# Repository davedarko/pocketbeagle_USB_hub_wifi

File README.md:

# pocketbeagle_USB_hub_wifi
WiFi cape for the pocketbeagle, connection over USB on the dual row header with an additional USB hub in between. Hub Chip is FE1.1S

find the documentation on [hackaday.io](https://hackaday.io/project/27600-wifi-and-usb-for-pocketbeagle)

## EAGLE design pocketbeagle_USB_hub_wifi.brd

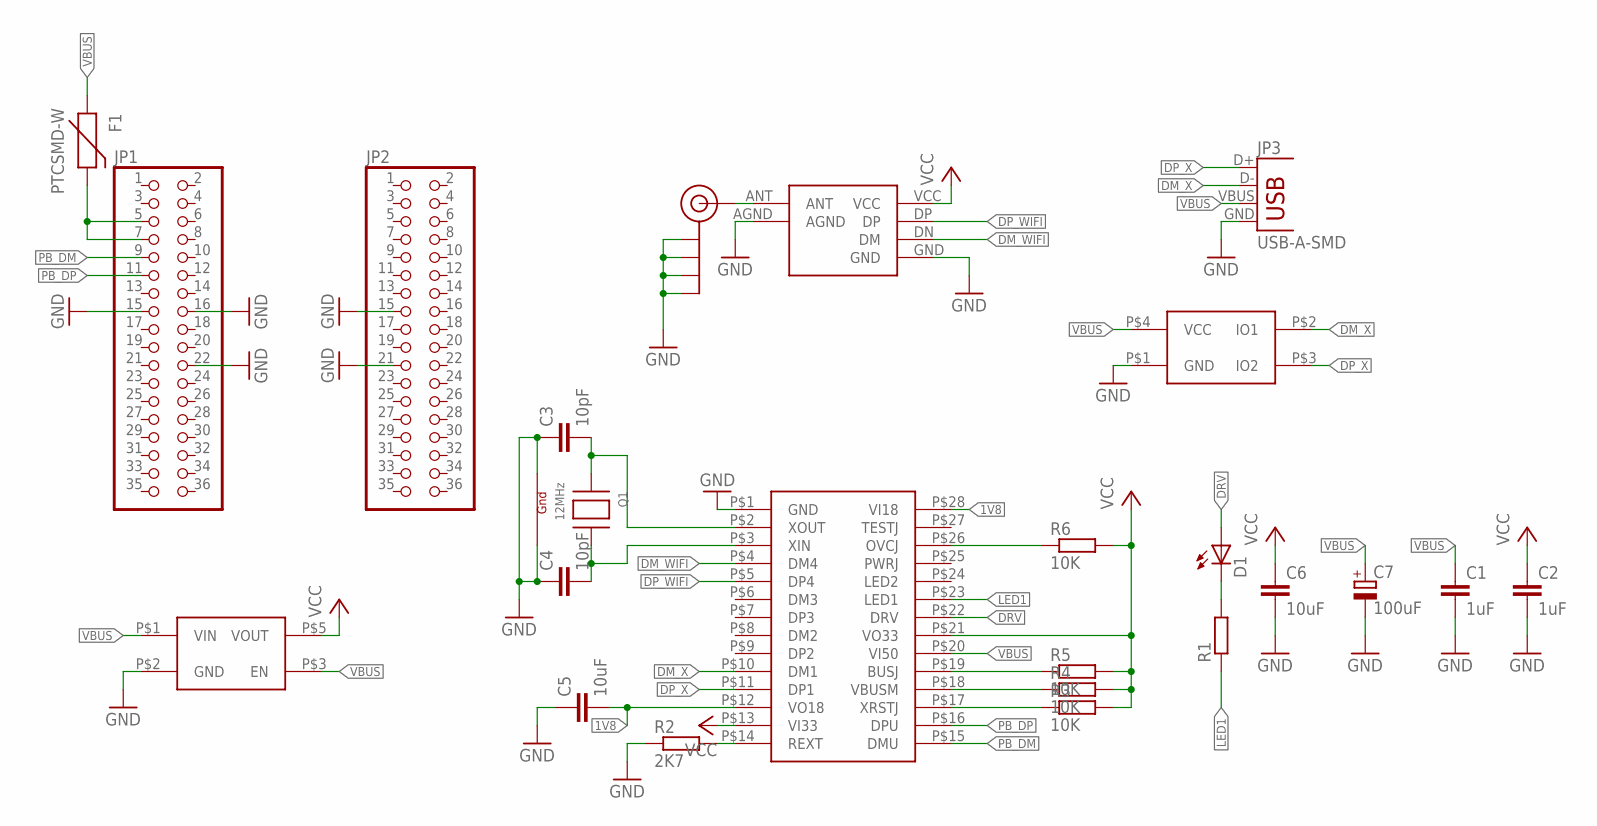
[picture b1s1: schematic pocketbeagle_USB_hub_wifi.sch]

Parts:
C1, C2: 1uF; ONEFITSALL
C3, C4: 10pF; C0603
C5, C6: 10uF; ONEFITSALL
C7: 100uF; 153CLV-0605
D1: LEDCHIP-LED0603; CHIP-LED0603
F1: PTCSMD-W; PTC-1206-WIDE
J$1: SMA_EDGE; SMA-EDGE
JP1, JP2: PINHD-2X18; 2X18
JP3: USB-A-SMD; USB-A-S-NOSILK-FEMALE
Q1: 12MHz; NX3225
R1: R-EU_R0603; R0603
R2: 2K7; R0603
R3, R4, R5, R6: 10K; R0603
U$1: RTL8188MODULE; RTL8188
U$2: FE1.1SSSOP28; FE1.1S
U$3: AP2112KAP2112K; AP2112
U$5: PRTR5V0U2X

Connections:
1V8: C5.P$2 (2), U$2.P$12 (VO18), U$2.P$28 (VI18)
DM_WIFI: U$1.DN (DM), U$2.P$4 (DM4)
DM_X: JP3.D-, U$2.P$10 (DM1), U$5.P$2 (IO1)
DP_WIFI: U$1.DP, U$2.P$5 (DP4)
DP_X: JP3.D+, U$2.P$11 (DP1), U$5.P$3 (IO2)
DRV: D1.A, U$2.P$22 (DRV)
GND: C1.P$2 (2), C2.P$2 (2), C3.1, C4.1, C5.P$1 (1), C6.P$2 (2), C7.-, J$1.GND@0 (GND), J$1.GND@1 (GND), J$1.GND@2 (GND), J$1.GND@3 (GND), JP1.15, JP1.16, JP1.22, JP2.15, JP2.21, JP3.GND, Q1.2 (G2), Q1.4 (G1), R2.1, U$1.AGND, U$1.GND, U$2.P$1 (GND), U$3.P$2 (GND), U$5.P$1 (GND)
LED1: R1.1, U$2.P$23 (LED1)
unnamed: J$1.SIG (SIGNAL), U$1.ANT
unnamed: D1.C, R1.2
unnamed: R3.1, U$2.P$17 (XRSTJ)
unnamed: C3.2, Q1.1 (X1), U$2.P$2 (XOUT)
unnamed: R4.1, U$2.P$18 (VBUSM)
unnamed: C4.2, Q1.3 (X2), U$2.P$3 (XIN)
unnamed: R2.2, U$2.P$14 (REXT)
unnamed: R5.1, U$2.P$19 (BUSJ)
unnamed: R6.1, U$2.P$26 (OVCJ)
PB_DM: JP1.9, U$2.P$15 (DMU)
PB_DP: JP1.11, U$2.P$16 (DPU)
PB_VBUS: F1.2, JP1.5, JP1.7
VBUS: C1.P$1 (1), C7.+, F1.1, JP3.VBUS, U$2.P$20 (VI50), U$3.P$1 (VIN), U$3.P$3 (EN), U$5.P$4 (VCC)
VCC: C2.P$1 (1), C6.P$1 (1), R3.2, R4.2, R5.2, R6.2, U$1.VCC, U$2.P$13 (VI33), U$2.P$21 (VO33), U$3.P$5 (VOUT)

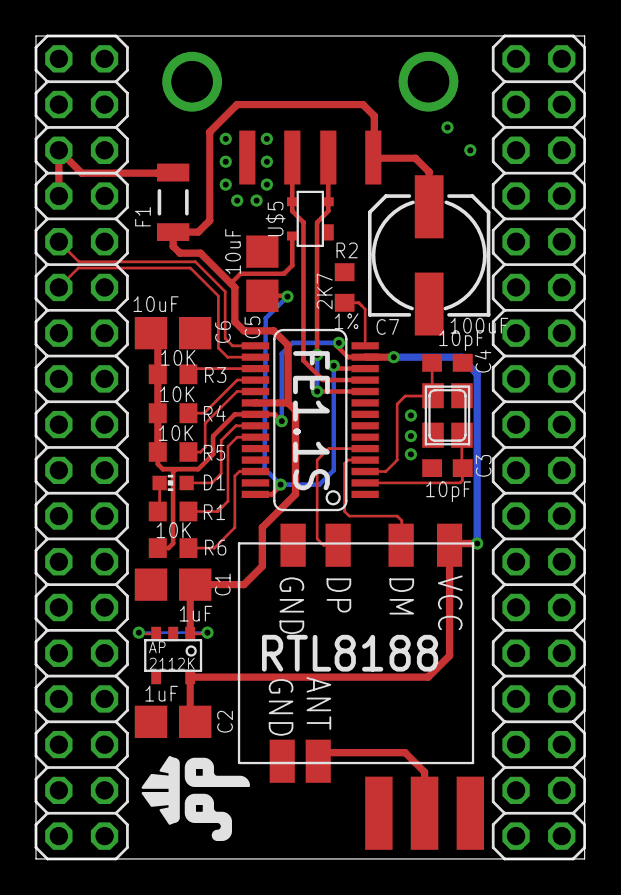
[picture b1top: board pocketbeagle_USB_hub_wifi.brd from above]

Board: 2 copper layers, 30.5 x 45.7 mm, 26 parts (1 on the bottom side), 22 nets.

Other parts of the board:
U$4, U$6: DAVEDARKO2_LOGO

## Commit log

2018-01-01 added design files and pdf

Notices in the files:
parts and their libraries:
SparkFun-Connectors: Licensing: Creative Commons ShareAlike 4.0 International - https://creativecommons.org/licenses/by-sa/4.0
diy-modules: Released under the Creative Commons Attribution 4.0 International License: http://creativecommons.org/licenses/by/4.0
